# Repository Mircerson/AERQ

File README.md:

# AERQ - Indoor air quality monitor

## Introduction
This is the repository for AERQ, a USB-powered indoor air quality monitor using the
[here](/PCB/101-5/) Bosch BME688 sensor, running on mbed os.
It measures temperature, humidity, CO2 and IAQ using the BSEC 2.x library.
This data is then sent to The Things Network.

## PCB
This project features a custom 4 layer board using the Seeed E5-LoRa and the Bosch BME688.
Two variants of the board, one with a chip antenna ( Linx USP-410 ) and one with a u.Fl connector.

Find more about the [STM32WL - Seeed E5-LoRa](https://www.seeedstudio.com/LoRa-E5-Wireless-Module-p-4745.html).

For the PCB with the integrated antenna, click here [here](/PCB/101-5/)

For the PCB with an external u.Fl connector, click [here](/PCB/101-3/)

## Code

The code runs on mbed os 6.15.1 with the latest LoRaWan stack.
Insert your TTN credentials in mbed_app.json before running the application.

This code features a custom target on mbed os which configures the RF switch properly and adds a few macros for the board.

See mbed_app.json and custom_targets.json for more details.

Thanks to [hallard](https://github.com/hallard/LoRa-E5-Breakout) for adding the support in the official mbed os custom target repository.

## Payload decoder for TTN
The payload should provide the following result:

```
function Decoder(bytes, port) {
  // Decode plain text; for testing only 
  //var statusFromDevice = String.fromCharCode.apply(null, bytes.slice(12,13))
  
  let StringOfBytes = String.fromCharCode.apply(null, bytes);
  
  var temperature;
  var humidity;
  var iaq;
  var iaqAccuracy;
  var CO2;
  
  const Array = StringOfBytes.split(" ");
  temperature = Array[0];
  humidity = Array[1];
  statusFromDevice = Array[2];
  iaq = Array[3];
  CO2 = Array[4];
  
  var statusToDisplay;
  
  if (statusFromDevice == "0"){
      statusToDisplay = "Device warming up";
  } else if(statusFromDevice == "1")
  {
      statusToDisplay = "Device is adjusting to the envinroment - calibrating";
  }else if(statusFromDevice == "2")
  {
      statusToDisplay = "Environment has changed - re-calibrating";
  }
  else if(statusFromDevice == "2")
  {
      statusToDisplay = "Environment has changed - re-calibrating";
  }
  else if(statusFromDevice == "3")
  {
      statusToDisplay = "Device is calibrated and running";
  }
  else if(statusFromDevice == "4")
  {
      statusToDisplay = "Error communicating with the IAQ sensor. Critical";
  }

  return {
      Humidity: humidity,
      //IAQAccuracy:String.fromCharCode.apply(null, bytes.slice(12,13)),
      IAQ:iaq,
      CO2:CO2,
      Temperature:temperature,
      Status:statusToDisplay
  };
}
```

## Android application

A simple KivyMD app was made for Android to receive packets:

## Azure IoT Central

Data can also be parsed through Azure IoT Hub to the Azure IoT Central

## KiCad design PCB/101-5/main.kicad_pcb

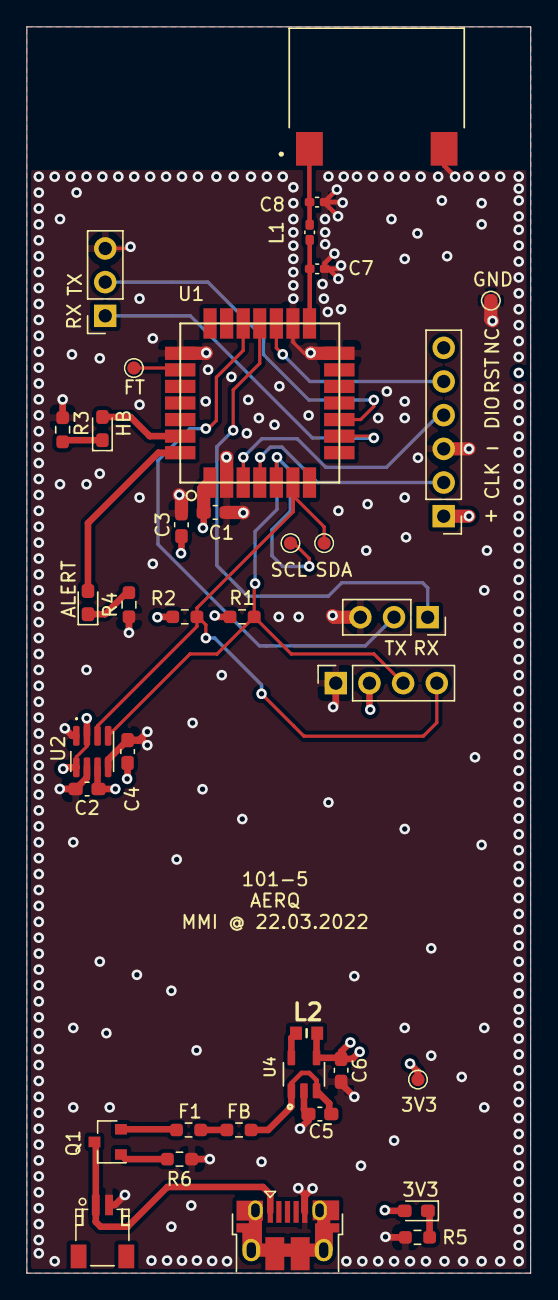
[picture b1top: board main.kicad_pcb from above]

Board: 4 copper layers, 38.0 x 94.0 mm, 37 parts (0 on the bottom side), 25 nets.

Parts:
3V1: PWR; LED_0603_1608Metric_Pad1.05x0.95mm_HandSolder
3V3_OUT1: 3V3_TP; TestPoint_Pad_D1.0mm
ALERT1: ALERT; LED_0603_1608Metric_Pad1.05x0.95mm_HandSolder
C1, C2, C4: 100nF; C_0603_1608Metric_Pad1.08x0.95mm_HandSolder
C3: 4.7uF; C_0603_1608Metric_Pad1.08x0.95mm_HandSolder
C5, C6: 10uF; C_0603_1608Metric_Pad1.08x0.95mm_HandSolder
C7, C8: DNP; C_0402_1005Metric_Pad0.74x0.62mm_HandSolder
E1: ANT-868-USP410; XDCR_ANT-868-USP410
F1: 300mA Fuse; R_0603_1608Metric_Pad0.98x0.95mm_HandSolder
FB1: FB; R_0603_1608Metric_Pad0.98x0.95mm_HandSolder
FT1: FT_TP; TestPoint_Pad_D1.0mm
GND1: GND; TestPoint_Pad_D1.0mm
HB1: HEARTBEAT; LED_0603_1608Metric_Pad1.05x0.95mm_HandSolder
J1: 1x6 header; PinHeader_1x06_P2.54mm_Vertical
J2: Conn_01x02_Male; JST_SH_SM02B-SRSS-TB_02x1.00mm_Angled
J4, J5: Conn_01x03; PinSocket_1x03_P2.54mm_Vertical
J6: Conn_01x04_Female; PinSocket_1x04_P2.54mm_Vertical
L1: DNP; L_0402_1005Metric_Pad0.77x0.64mm_HandSolder
L2: 2.2uH; INDC1608X95N
Q1: DMG2305UX-13-TestLibrary; SOT-23
R1, R2: 4.7k; R_0603_1608Metric_Pad0.98x0.95mm_HandSolder
R3, R4, R5: 1.8k; R_0603_1608Metric_Pad0.98x0.95mm_HandSolder
R6: 100k; R_0603_1608Metric_Pad0.98x0.95mm_HandSolder
SCL1: SCL_TP; TestPoint_Pad_D1.0mm
SDA1: SDA_TP; TestPoint_Pad_D1.0mm
U1: LoRa-E5
U2: BME688; Bosch_LGA-8_3x3mm_P0.8mm_ClockwisePinNumbering
U4: SC4626ZSKTRT; SOT95P280X145-5N
USB_PWR1: USB_B_Micro; USB_Micro-B_Amphenol_10103594-0001LF_Horizontal

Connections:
+3V3: 3V1.2, 3V3_OUT1.1, C1.1, C2.1, C3.1, C4.1, C6.2, J1.1, J6.2, L2.2, R1.1, R2.1, U1.1, U2.2, U2.6, U2.8, U4.4
FT: FT1.1, U1.23
GND: C1.2, C2.2, C3.2, C4.2, C5.1, C6.1, C7.2, C8.2, E1.2, GND1.1, J1.3, J2.2, J4.3, J5.3, J6.1, R3.1, R4.1, R5.1, R6.2, U1.2, U1.14, U1.16, U1.22, U2.1, U2.5, U2.7, U4.2, USB_PWR1.5
HEARTBEAT_LED: HB1.2, U1.27
I2C_SCL: J6.3, R1.2, SCL1.1, U1.5, U2.4
I2C_SDA: J6.4, R2.2, SDA1.1, U1.6, U2.3
LED_ALERT: ALERT1.2, U1.28
unnamed: 3V1.1, R5.2
unnamed: ALERT1.1, R4.2
unnamed: C5.2, FB1.2, U4.1, U4.3
unnamed: C8.1, E1.1, L1.2
unnamed: F1.1, Q1.2
unnamed: F1.2, FB1.1
unnamed: HB1.1, R3.2
unnamed: L2.1, U4.5
unnamed: Q1.1, R6.1
RF_ANTENNA: C7.1, L1.1, U1.15
RST: J1.5, U1.17
SWCLK: J1.2, U1.4
SWDIO: J1.4, U1.3
UART1_RX: J4.1, U1.9
UART1_TX: J4.2, U1.10
USART2_RX: J5.1, U1.18
USART2_TX: J5.2, U1.19
VDD: J2.1, Q1.3, USB_PWR1.1

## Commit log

2022-04-20 Add PCB
2022-04-20 Readme
